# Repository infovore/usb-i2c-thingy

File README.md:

# usb-i2c-thingy

An I2C dongle designed to interface devices like [monome norns][norns] with 3.3V i2c.

3.5mm stereo jack uses _tip_ for `SDA` and _ring_ for `SCL`.

Take a [digispark][digispark]; replace the usb tab with a micro-usb socket; add a 3.5mm jack for I2C connection; add I2C level shifting as per [this datasheet][level-shifting]. Add its own 3.3V regulator for the level-shfiting.

You can then flash this pseudo-digispark with the [I2C-Tiny-USB firmware][i2ctiny], which is supported by the Linux kernel.

## STATE

nowhere near finished don't even think about using it.

## TODO

- ~~replace 402 parts with 603~~
- ~~connect SDA/SCL to pins~~
- break out programming header?
- caps for 3.3V regulator?
- add CCBYSA credits to board
- add jack details (tip/ring) to board
- routing
- how do you program it? Mark the pins.

## LICENSE

CC-BY-SA; digispark accredition to be supplied in fullness of time

[digispark]: http://digistump.com/products/1
[norns]: https://monome.org/docs/norns/
[i2ctiny]: https://github.com/harbaum/I2C-Tiny-USB/blob/master/digispark/README.md
[level-shifting]: https://www.nxp.com/docs/en/application-note/AN10441.pdf

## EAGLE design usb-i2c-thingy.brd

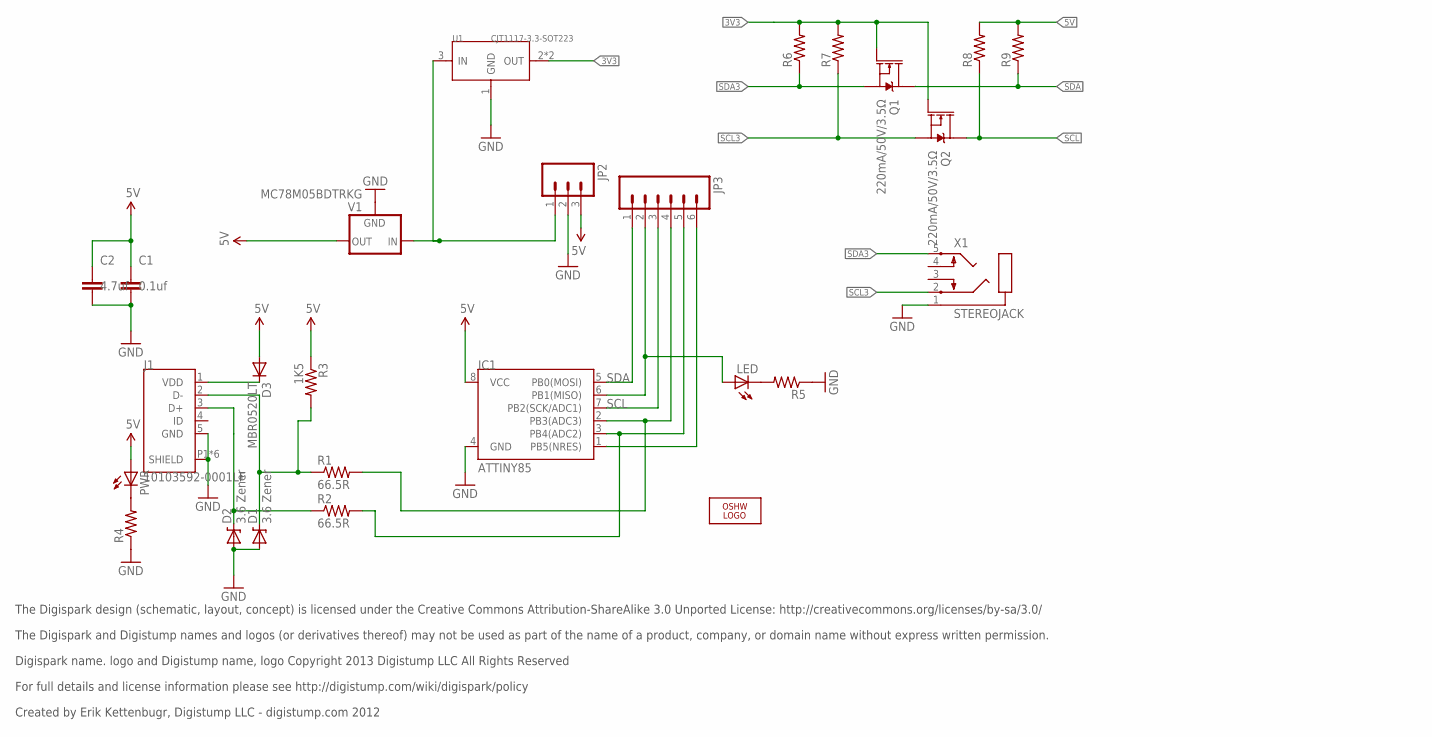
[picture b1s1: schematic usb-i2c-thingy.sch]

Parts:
C1: 0.1uf; C0603
C2: 4.7uf; C0603
D1, D2: 3.6 Zener; SOD-323
D3: MBR0520LT; SOD123
IC1: ATTINY85; SO08-EIAJ
J1: 10103592-0001LF; AMPHENOL_10103592-0001LF
JP2: M03PTH; 1X03
JP3: M06SIP; 1X06
LED: LED0603; LED-0603
LOGO2: LOGO-OSHW-10MILX0200-NT; OSHW_10X200_NOTEXT
PWR: LED0603; LED-0603
Q1, Q2: 220mA/50V/3.5Ω; SOT23-3
R1, R2: 66.5R; R0603
R3: 1K5; R0603
R4, R5, R6, R7, R8, R9: R-US_R0603; R0603
U1: CJT1117-3.3-SOT223; SOT-223
V1: MC78M05BDTRKG; DPACK
X1: STEREOJACK; STX3100

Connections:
3V3: Q1.1 (G), Q2.1 (G), R6.2, R7.2, U1.2 (OUT), U1.TER (OUT)
5V: C1.1, C2.1, D3.A, IC1.8 (VCC), JP2.3, PWR.A, R3.1, R8.2, R9.2, V1.3 (OUT)
GND: C1.2, C2.2, D1.2 (A), D2.2 (A), IC1.4 (GND), J1.5 (GND), J1.P1 (SHIELD), J1.P2 (SHIELD), J1.P3 (SHIELD), J1.P4 (SHIELD), J1.P5 (SHIELD), J1.P6 (SHIELD), JP2.2, R4.1, R5.1, U1.1 (GND), V1.4 (GND), X1.1
unnamed: IC1.2 (PB3(ADC3)), JP3.4, R1.2
unnamed: IC1.6 (PB1(MISO)), JP3.2, LED.A
unnamed: IC1.3 (PB4(ADC2)), JP3.5, R2.2
unnamed: IC1.1 (PB5(NRES)), JP3.6
unnamed: D1.1 (C), J1.2 (D-), R1.1, R3.2
unnamed: D2.1 (C), J1.3 (D+), R2.1
unnamed: LED.C, R5.2
unnamed: JP2.1, U1.3 (IN), V1.1 (IN)
unnamed: D3.C, J1.1 (VDD)
unnamed: PWR.C, R4.2
SCL: IC1.7 (PB2(SCK/ADC1)), JP3.3, Q2.3 (D), R8.1
SCL3: Q2.2 (S), R7.1, X1.2
SDA: IC1.5 (PB0(MOSI)), JP3.1, Q1.3 (D), R9.1
SDA3: Q1.2 (S), R6.1, X1.5

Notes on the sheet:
The Digispark design (schematic, layout, concept) is licensed under the Creative Commons Attribution-ShareAlike 3.0 Unported License: http://creativecommons.org/licenses/by-sa/3.0/
The Digispark and Digistump names and logos (or derivatives thereof) may not be used as part of the name of a product, company, or domain name without express written permission.
Digispark name. logo and Digistump name, logo Copyright 2013 Digistump LLC All Rights Reserved
For full details and license information please see http://digistump.com/wiki/digispark/policy
Created by Erik Kettenbugr, Digistump LLC - digistump.com 2012

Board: 2 copper layers, 26 parts (1 on the bottom side), 17 nets, no tracks yet.

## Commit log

2019-10-12 Initial commit.
2019-10-12 Ignore EAGLE temp files.
2019-10-12 Change dimensions, add 603 parts, add SDA/SCL hookup on schematic, jiggle around layout.
2019-10-12 Correct norns link.
2019-10-12 Remove DS stuff from board, be sure to credit as part of CCBYSA licensing in future.
2019-10-12 M3 holes, rounded corners.

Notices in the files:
parts and their libraries:
SparkFun: Licensing: CC v3.0 Share-Alike You are welcome to use this library for commercial purposes.
SparkFun-DiscreteSemi: Licensing: Creative Commons ShareAlike 4.0 International - https://creativecommons.org/licenses/by-sa/4.0
